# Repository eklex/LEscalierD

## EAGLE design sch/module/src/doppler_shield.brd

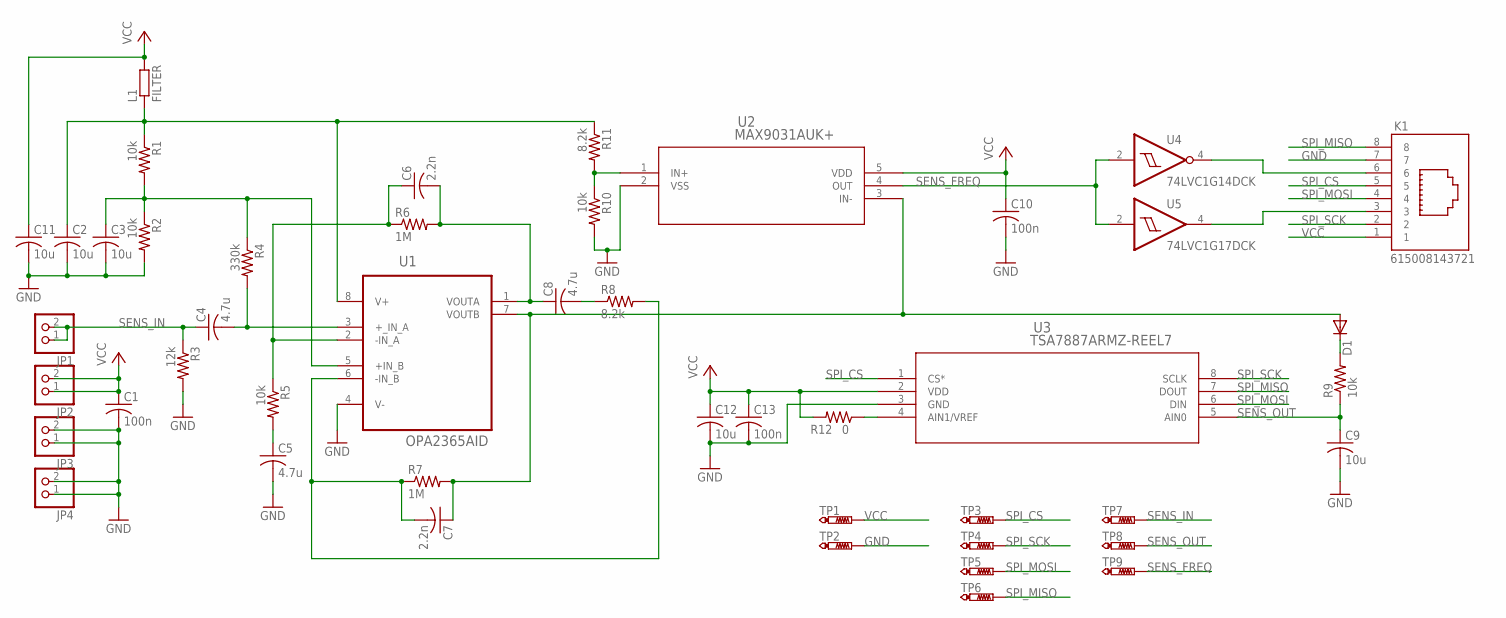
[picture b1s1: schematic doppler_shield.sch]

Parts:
C1, C10, C13: 100n; C0805
C2, C3, C9, C11, C12: 10u; C0805
C4, C5, C8: 4.7u; C0805
C6, C7: 2.2n; C0805
D1: DIODE-DO214AC; DO214AC
JP1, JP2, JP3, JP4: PINHD-1X2; 1X02
K1: 615008143721
L1: FILTER; R0805
R1, R2, R5, R9, R10: 10k; R0805
R3: 12k; R0805
R4: 330k; R0805
R6, R7: 1M; R0805
R8, R11: 8.2k; R0805
R12: 0; R0805
TP1, TP2, TP3, TP4, TP5, TP6, TP7, TP8, TP9: PTR1B1,27; B1,27
U1: OPA2365AID; SOIC127P600X175-8N
U2: MAX9031AUK+; 21-0057F
U3: TSA7887ARMZ-REEL7; RM_8
U4: 74LVC1G14DCK; SC70-5
U5: 74LVC1G17DCK; SC70-5

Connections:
GND: C1.2, C2.2, C3.2, C5.2, C9.2, C10.2, C11.2, C12.2, C13.2, JP3.1, JP3.2, JP4.1, JP4.2, K1.7, R2.2, R3.2, R10.2, TP2.TP, U1.4 (V-), U2.2 (VSS), U3.3 (GND), U4.3 (GND), U5.3 (GND)
unnamed: C3.1, R1.2, R2.1, R4.1, U1.5 (+IN_B)
unnamed: R10.1, R11.2, U2.1 (IN+)
unnamed: D1.C, R9.2
unnamed: R12.1, U3.4 (AIN1/VREF)
unnamed: K1.6, U4.4 (O)
unnamed: K1.3, U5.4 (O)
unnamed: C4.2, R4.2, U1.3 (+_IN_A)
unnamed: C5.1, R5.2
unnamed: C6.1, R5.1, R6.1, U1.2 (-IN_A)
unnamed: C6.2, C8.1, R6.2, U1.1 (VOUTA)
unnamed: C8.2, R8.1
unnamed: C7.2, R7.1, R8.2, U1.6 (-IN_B)
unnamed: C7.1, D1.A, R7.2, U1.7 (VOUTB), U2.3 (IN-)
SENS_FREQ: TP9.TP, U2.4 (OUT), U4.2 (I), U5.2 (I)
SENS_IN: C4.1, JP1.1, JP1.2, R3.1, TP7.TP
SENS_OUT: C9.1, R9.1, TP8.TP, U3.5 (AIN0)
SPI_CS: K1.5, TP3.TP, U3.1 (CS*)
SPI_MISO: K1.8, TP6.TP, U3.7 (DOUT)
SPI_MOSI: K1.4, TP5.TP, U3.6 (DIN)
SPI_SCK: K1.2, TP4.TP, U3.8 (SCLK)
VCC: C1.1, C10.1, C11.1, C12.1, C13.1, JP2.1, JP2.2, K1.1, L1.2, R12.2, TP1.TP, U2.5 (VDD), U3.2 (VDD), U4.5 (VCC), U5.5 (VCC)
VCC_AMP: C2.1, L1.1, R1.1, R11.1, U1.8 (V+)

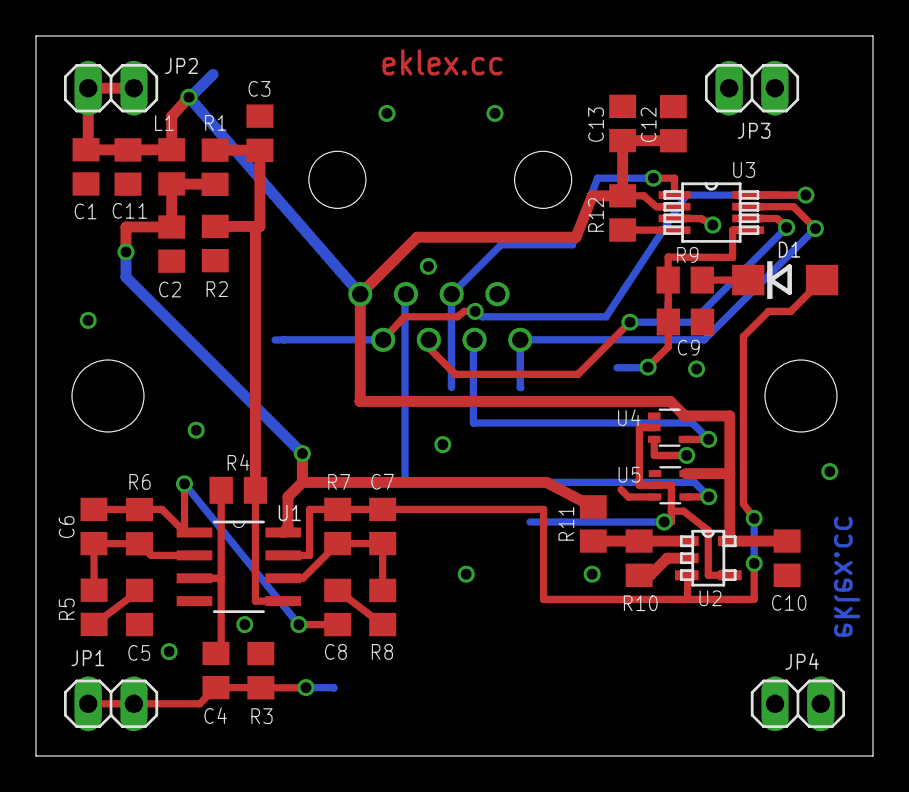
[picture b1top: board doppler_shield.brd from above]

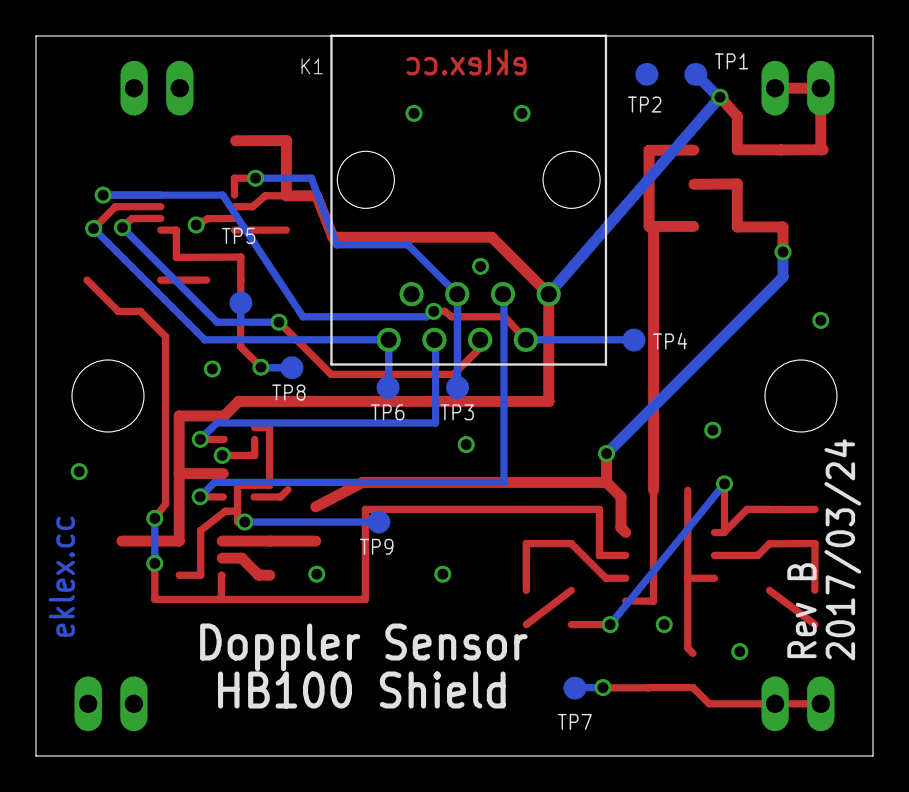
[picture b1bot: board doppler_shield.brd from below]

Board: 2 copper layers, 46.5 x 40.0 mm, 46 parts (10 on the bottom side), 23 nets.

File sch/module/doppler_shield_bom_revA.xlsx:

Part | Quantity | Value | Eagle Device | Package | Part Number | Reference | Description
C1, C10, C13 | 3 | 100n | C-USC0805 | C0805 | 399-1170-1-ND | SENS-C100N | CAP CER 0.1UF 50V X7R 0805
C2, C3, C9, C11, C12 | 5 | 10u | C-USC0805 | C0805 | 490-3886-1-ND | SENS-C10U | CAP CER 10UF 16V X5R 0805
C4, C5, C8 | 3 | 4.7u | C-USC0805 | C0805 | 490-3335-1-ND | SENS-C4.7U | CAP CER 4.7UF 25V X5R 0805
C6, C7 | 2 | 2.2n | C-USC0805 | C0805 | 399-1151-1-ND | SENS-C2.2N | CAP CER 2200PF 50V X7R 0805
R1, R2, R5, R9, R10 | 5 | 10k | R-US_R0805 | R0805 | P10.0KCCT-ND | SENS-R10K | RES SMD 10K OHM 1% 1/8W 0805
R3 | 1 | 12k | R-US_R0805 | R0805 | P12.0KCCT-ND | SENS-R12K | RES SMD 12K OHM 1% 1/8W 0805
R4 | 1 | 330k | R-US_R0805 | R0805 | P330KCCT-ND | SENS-R330K | RES SMD 330K OHM 1% 1/8W 0805
R6, R7 | 2 | 1M | R-US_R0805 | R0805 | P1.00MCCT-ND | SENS-R1M | RES SMD 1M OHM 1% 1/8W 0805
R8, R11 | 2 | 8.2k | R-US_R0805 | R0805 | P8.20KCCT-ND | SENS-R8.2K | RES SMD 8.2K OHM 1% 1/8W 0805
R12 | 1 | 0 | R-US_R0805 | R0805 | P0.0ACT-ND | SENS-R0 | RES SMD 0.0 OHM JUMPER 1/8W 0805
L1 | 1 | FILTER | R-EU_R0805 | R0805 | HZ0805D102R-10 | SENS-L1 | FERRITE BEAD 1 KOHM 0805 1LN
U1 | 1 | OPA2365AID | OPA2365AID | SOIC127 | OPA2365AIDR | SENS-AOP | IC OPAMP GP 50MHZ RRO 8SOIC
U2 | 1 | MAX9031AUK+ | MAX9031AUK+ | SOT-23-5 | MAX9031AUK+TCT-ND | SENS-CMP | IC COMPARATOR VOLT SGL SOT23-5
U3 | 1 | TSA7887ARMZ-REEL7 | AD7887ARMZ-REEL7 | 8-MSOP | TSA7887ARMZ-REEL | SENS-ADC | IC ADC 12BIT 125KSPS 2CH 8-MSOP
U4 | 1 | 74LVC1G14DCK | 74LVC1G14DCK | SC-70-5 | SN74LVC1G14DCKR | SENS-INV | IC SGL SCHMT-TRIG INVERT SC70-5
U5 | 1 | 74LVC1G17DCK | 74LVC1G17DCK | SC-70-5 | SN74LVC1G17DCKR | SENS-BUF | IC BUFFER SCHMIT TRIG SC70-5
D1 | 1 | - | DIODE-DO214AC | DO-214AC | STPS1L30A | SENS-D1 | DIODE SCHOTTKY 30V 1A SMA
K1 | 1 | - | 615008143721 | - | 615008143721 | SENS-RJ45 | CONN MOD JACK 8P8C R/A UNSHLD
JP1, JP2, JP3, JP4 | 4 | - | PINHD-1X2 | 1X02 | Aliexpress | SENS-CONN | PIN HEADER 2.54MM WIDTH 20MM LONG

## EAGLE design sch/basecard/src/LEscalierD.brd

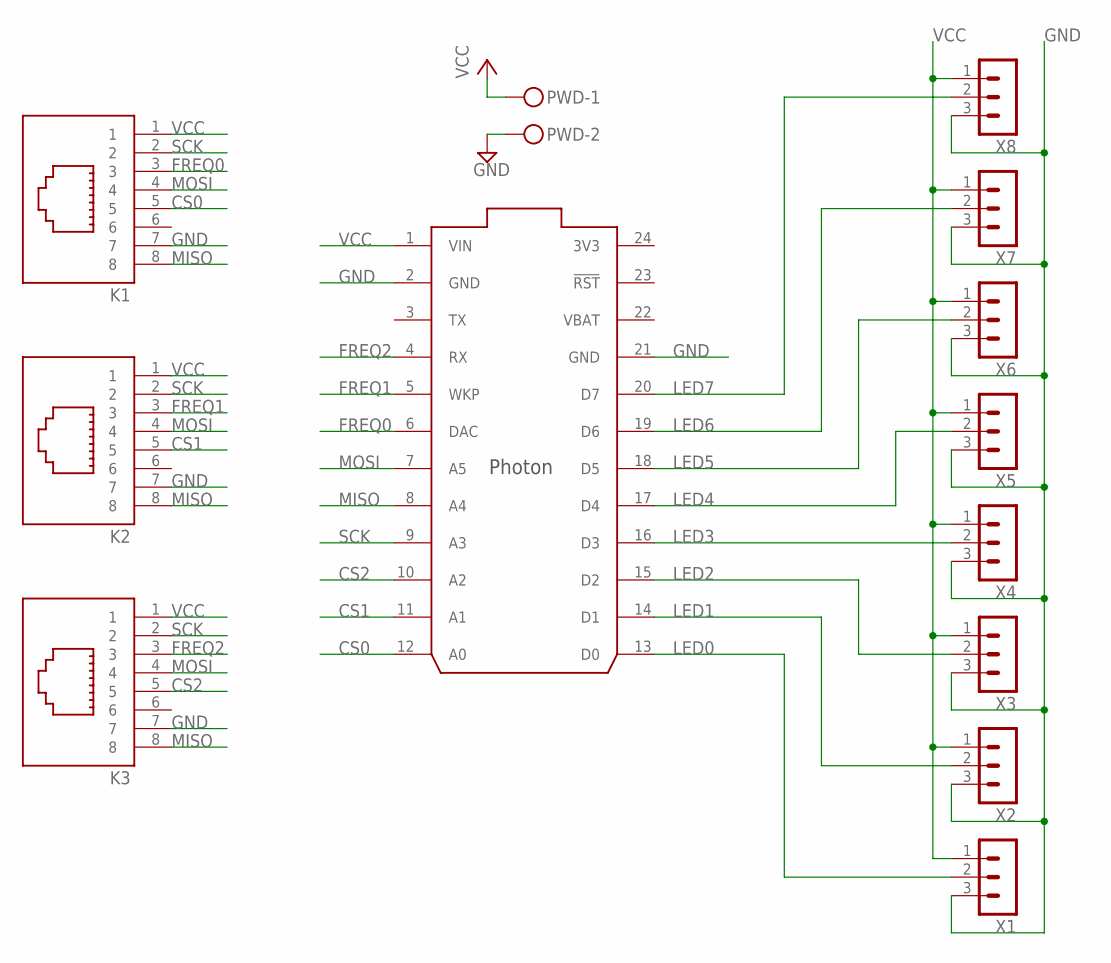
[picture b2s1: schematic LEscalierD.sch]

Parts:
K1, K2, K3: 615008144221
PWD: MKDSN1,5/2-5,08
U1: PHOTON_WITH_HEADERS; PHOTON
X1, X2, X3, X4, X5, X6, X7, X8: B3B-XASTD; B3B-XA

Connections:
3V3: U1.24 (3V3)
CS0: K1.5, U1.12 (A0)
CS1: K2.5, U1.11 (A1)
CS2: K3.5, U1.10 (A2)
FREQ0: K1.3, U1.6 (DAC)
FREQ1: K2.3, U1.5 (WKP)
FREQ2: K3.3, U1.4 (RX)
GND: K1.7, K2.7, K3.7, PWD.2, U1.2 (GND), U1.21 (GND), X1.3, X2.3, X3.3, X4.3, X5.3, X6.3, X7.3, X8.3
LED0: U1.13 (D0), X1.2
LED1: U1.14 (D1), X2.2
LED2: U1.15 (D2), X3.2
LED3: U1.16 (D3), X4.2
LED4: U1.17 (D4), X5.2
LED5: U1.18 (D5), X6.2
LED6: U1.19 (D6), X7.2
LED7: U1.20 (D7), X8.2
MISO: K1.8, K2.8, K3.8, U1.8 (A4)
MOSI: K1.4, K2.4, K3.4, U1.7 (A5)
SCK: K1.2, K2.2, K3.2, U1.9 (A3)
VBAT: U1.22 (VBAT)
VCC: K1.1, K2.1, K3.1, PWD.1, U1.1 (VIN), X1.1, X2.1, X3.1, X4.1, X5.1, X6.1, X7.1, X8.1

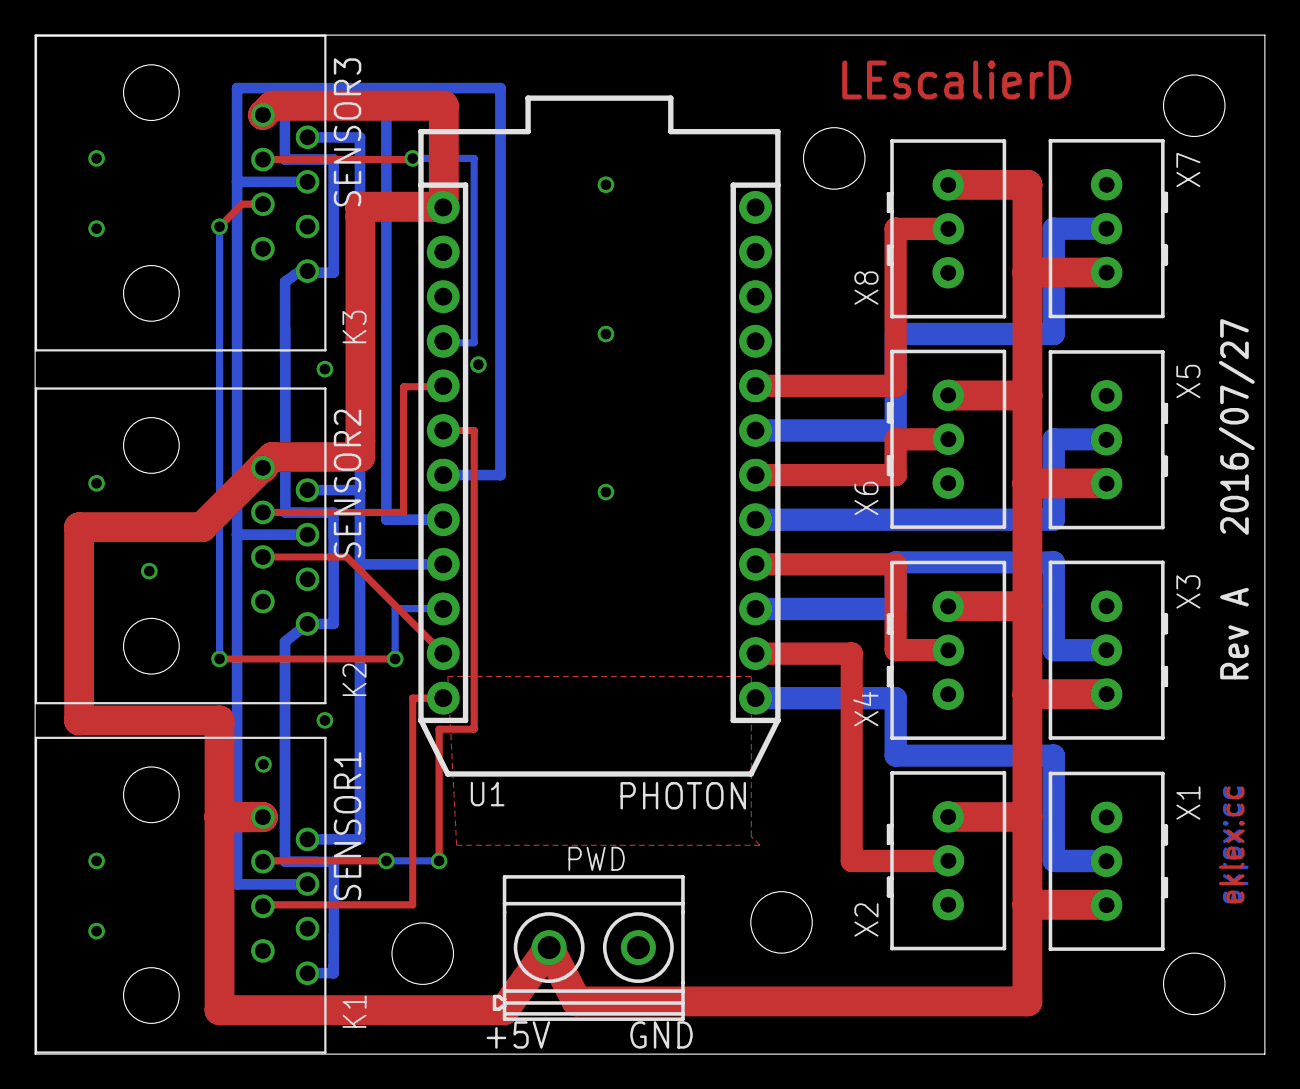
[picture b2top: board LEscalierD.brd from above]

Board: 2 copper layers, 70.0 x 58.0 mm, 13 parts (0 on the bottom side), 19 nets.

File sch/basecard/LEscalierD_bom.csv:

"Part";"Value";"Device";"Package";"Description";"MK";"OC_DIGIKEY";"REF";"VEN";
"K1";"";"615008144221";"615008144221";"WR-MJ Vertical Plastic 8P8C Modular Jack With Ears, 8 pins=>Code : Con_I-O_MJ-V_Plastic_615008144221";"";"";"";"";
"K2";"";"615008144221";"615008144221";"WR-MJ Vertical Plastic 8P8C Modular Jack With Ears, 8 pins=>Code : Con_I-O_MJ-V_Plastic_615008144221";"";"";"";"";
"K3";"";"615008144221";"615008144221";"WR-MJ Vertical Plastic 8P8C Modular Jack With Ears, 8 pins=>Code : Con_I-O_MJ-V_Plastic_615008144221";"";"";"";"";
"PWD";"";"MKDSN1,5/2-5,08";"MKDSN1,5/2-5,08";"MKDSN 1,5/ 2-5,08 Printklemme";"";"";"";"";
"U1";"";"PHOTON_WITH_HEADERS";"PHOTON";"";"";"";"";"";
"X1";"B3B-XASTD";"B3B-XASTD";"B3B-XA";"JST XA 3POS 2.5MM";"DIGIKEY";"455-1990-ND";"B03B-XASK-1";"JST";
"X2";"B3B-XASTD";"B3B-XASTD";"B3B-XA";"JST XA 3POS 2.5MM";"DIGIKEY";"455-1990-ND";"B03B-XASK-1";"JST";
"X3";"B3B-XASTD";"B3B-XASTD";"B3B-XA";"JST XA 3POS 2.5MM";"DIGIKEY";"455-1990-ND";"B03B-XASK-1";"JST";
"X4";"B3B-XASTD";"B3B-XASTD";"B3B-XA";"JST XA 3POS 2.5MM";"DIGIKEY";"455-1990-ND";"B03B-XASK-1";"JST";
"X5";"B3B-XASTD";"B3B-XASTD";"B3B-XA";"JST XA 3POS 2.5MM";"DIGIKEY";"455-1990-ND";"B03B-XASK-1";"JST";
"X6";"B3B-XASTD";"B3B-XASTD";"B3B-XA";"JST XA 3POS 2.5MM";"DIGIKEY";"455-1990-ND";"B03B-XASK-1";"JST";
"X7";"B3B-XASTD";"B3B-XASTD";"B3B-XA";"JST XA 3POS 2.5MM";"DIGIKEY";"455-1990-ND";"B03B-XASK-1";"JST";
"X8";"B3B-XASTD";"B3B-XASTD";"B3B-XA";"JST XA 3POS 2.5MM";"DIGIKEY";"455-1990-ND";"B03B-XASK-1";"JST";

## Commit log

2016-01-10 intial baseline
2016-01-11 first RC with working acc.
2016-02-07 mod to catch accel hang
2016-02-27 added autocovariance algo
2016-02-28 added new cloud commands
2016-02-28 cleaned-up accelerometer code
2016-02-29 added led specific files
2016-04-10 added support for command read back
2016-07-23 replaced accelero with ADC
2016-07-23 added center and sides animations and fixed cone animation
2016-10-03 adjusted pin configuration for final PCB
2016-11-27 added cascade opening
2016-11-27 renamed project from Strips to LEscalierD
2016-11-27 added the GNU GPLv3 license
2016-11-27 moved source code to src directory
2016-12-04 added schematic and pcb for basecard and module
2017-03-25 Updated PCB of module card (doppler shield) to revB
    - Fixed JB3 position
    - Added 2 holes aligned on sensor's holes
    - No changes in schematic and BOM
    - Updated revision of SCH, PCB and BOM to revB
2020-01-21 Added tree opening and rainbow mode
    - Add tree opening
    - Add dynamic rainbow mode (instead of built-in option)
    - Add copyright to all files to match project license
    Note that FastLED project is MIT, and the copyright is not hold by me

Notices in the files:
parts and their libraries:
Input-Output_Connectors_rev15d: Copyright: Würth Elektronik
COPYRIGHT: Copyright (C) 2015 Accelerated Designs. All rights reserved
